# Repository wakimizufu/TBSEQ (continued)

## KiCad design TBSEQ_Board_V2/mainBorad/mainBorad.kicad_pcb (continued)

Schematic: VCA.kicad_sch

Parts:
C20, C21: 0.01uF; C_Rect_L7.2mm_W2.5mm_P5.00mm_FKS2_FKP2_MKS2_MKP2
C36: 0.033uF; C_Rect_L7.2mm_W2.5mm_P5.00mm_FKS2_FKP2_MKS2_MKP2
C37: 10uF/16V; CP_Radial_D4.0mm_P2.00mm
C41: 0.1uF; C_Rect_L7.2mm_W2.5mm_P5.00mm_FKS2_FKP2_MKS2_MKP2
C42: 1uF/50V; CP_Radial_D5.0mm_P2.00mm
D27, D35, D36: D; D_A-405_P2.54mm_Vertical_AnodeUp
IC15: CA3080A; DIP-8_W7.62mm
J4: Conn_01x02_Pin; PinHeader_1x02_P2.54mm_Horizontal
Q31: PNP; TO-92_HandSolder
Q32: NPN; TO-92_HandSolder
R119: 47K; R_Axial_DIN0207_L6.3mm_D2.5mm_P2.54mm_Vertical
R120, R134: 22K; R_Axial_DIN0207_L6.3mm_D2.5mm_P2.54mm_Vertical
R121, R131: 220K; R_Axial_DIN0207_L6.3mm_D2.5mm_P2.54mm_Vertical
R122: 100K; R_Axial_DIN0207_L6.3mm_D2.5mm_P2.54mm_Vertical
R123: 1.5M; R_Axial_DIN0207_L6.3mm_D2.5mm_P2.54mm_Vertical
R124, R125, R126, R133: 2.2K; R_Axial_DIN0207_L6.3mm_D2.5mm_P2.54mm_Vertical
R130, R132: 100; R_Axial_DIN0207_L6.3mm_D2.5mm_P2.54mm_Vertical
VCA_C_1, VCA_C_2: 10uF/16V; CP_Radial_D4.0mm_P2.00mm
VCA_IC_1: Opamp_Dual; DIP-8_W7.62mm
VCA_R1: 10K; R_Axial_DIN0207_L6.3mm_D2.5mm_P2.54mm_Vertical
VCA_R2: 100; R_Axial_DIN0207_L6.3mm_D2.5mm_P2.54mm_Vertical
VCA_R3, VCA_R5: 47K; R_Axial_DIN0207_L6.3mm_D2.5mm_P2.54mm_Vertical
VCA_R4, VCA_R6, VCA_R7: 100K; R_Axial_DIN0207_L6.3mm_D2.5mm_P2.54mm_Vertical

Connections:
A+5.333V: R126.2, VCA_IC_1.6 (-), VCA_R1.2; also elsewhere on the board
A+12V: IC15.7 (V+), R123.1, VCA_IC_1.8 (V+), VCA_R6.1; also elsewhere on the board
A+LineOut: J4.1, VCA_C_1.2, VCA_R4.1; also elsewhere on the board
A+VCA-Reso_ACC: R119.2; also elsewhere on the board
A+VCA_Control: IC15.5 (BIAS), VCA_R5.1
A+VCA_Env: D36.2 (A); also elsewhere on the board
A+VCA_Resonance: C20.1; also elsewhere on the board
A+VCA_Signal: C21.1; also elsewhere on the board
A+VCA_Trig: D35.2 (A); also elsewhere on the board
GNDA: C36.1, C37.2, C41.1, C42.2, IC15.4 (V-), J4.2, R130.2, VCA_IC_1.4 (V-), VCA_R4.2, VCA_R7.2; also elsewhere on the board
unnamed: C20.2, R122.2
unnamed: C21.2, R121.2
unnamed: C36.2, R119.1, R120.2
unnamed: C37.1, R124.2, R125.2, R126.1
unnamed: D27.2 (A), R120.1
unnamed: D27.1 (K), Q31.2 (C), VCA_R5.2
unnamed: D35.1 (K), R133.2
unnamed: D36.1 (K), R134.2
unnamed: IC15.3 (+), R121.1, R122.1, R124.1
unnamed: IC15.2 (-), R125.1
unnamed: IC15.6, VCA_C_2.1
unnamed: C42.1, Q31.3 (B), R123.2, R132.1
unnamed: Q31.1 (E), R131.1
unnamed: C41.2, Q32.3 (B), R134.1
unnamed: Q32.2 (C), R132.2
unnamed: Q32.1 (E), R130.1
unnamed: R131.2, R133.1
unnamed: VCA_C_1.1, VCA_R2.1
unnamed: VCA_IC_1.1, VCA_R2.2, VCA_R3.1
unnamed: VCA_C_2.2, VCA_IC_1.3 (+), VCA_R6.2, VCA_R7.1
unnamed: VCA_IC_1.2 (-), VCA_R1.1, VCA_R3.2
unnamed: VCA_IC_1.5 (+), VCA_IC_1.7

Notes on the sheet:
VOLUME
toJackBorad

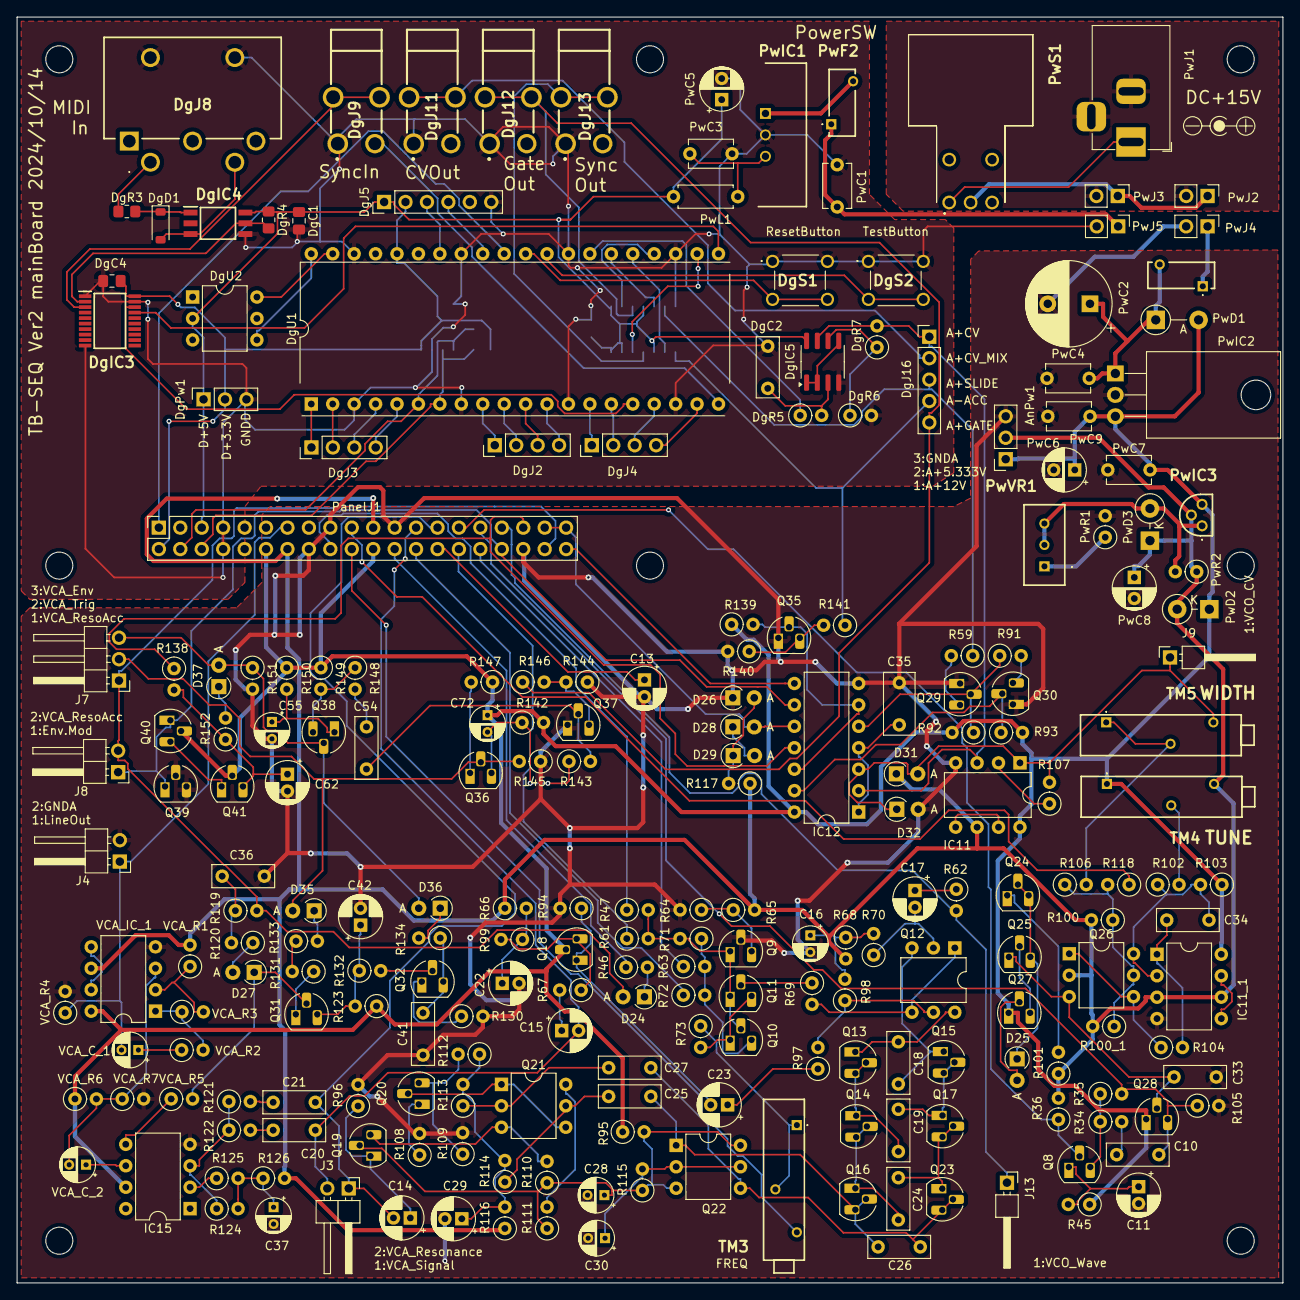
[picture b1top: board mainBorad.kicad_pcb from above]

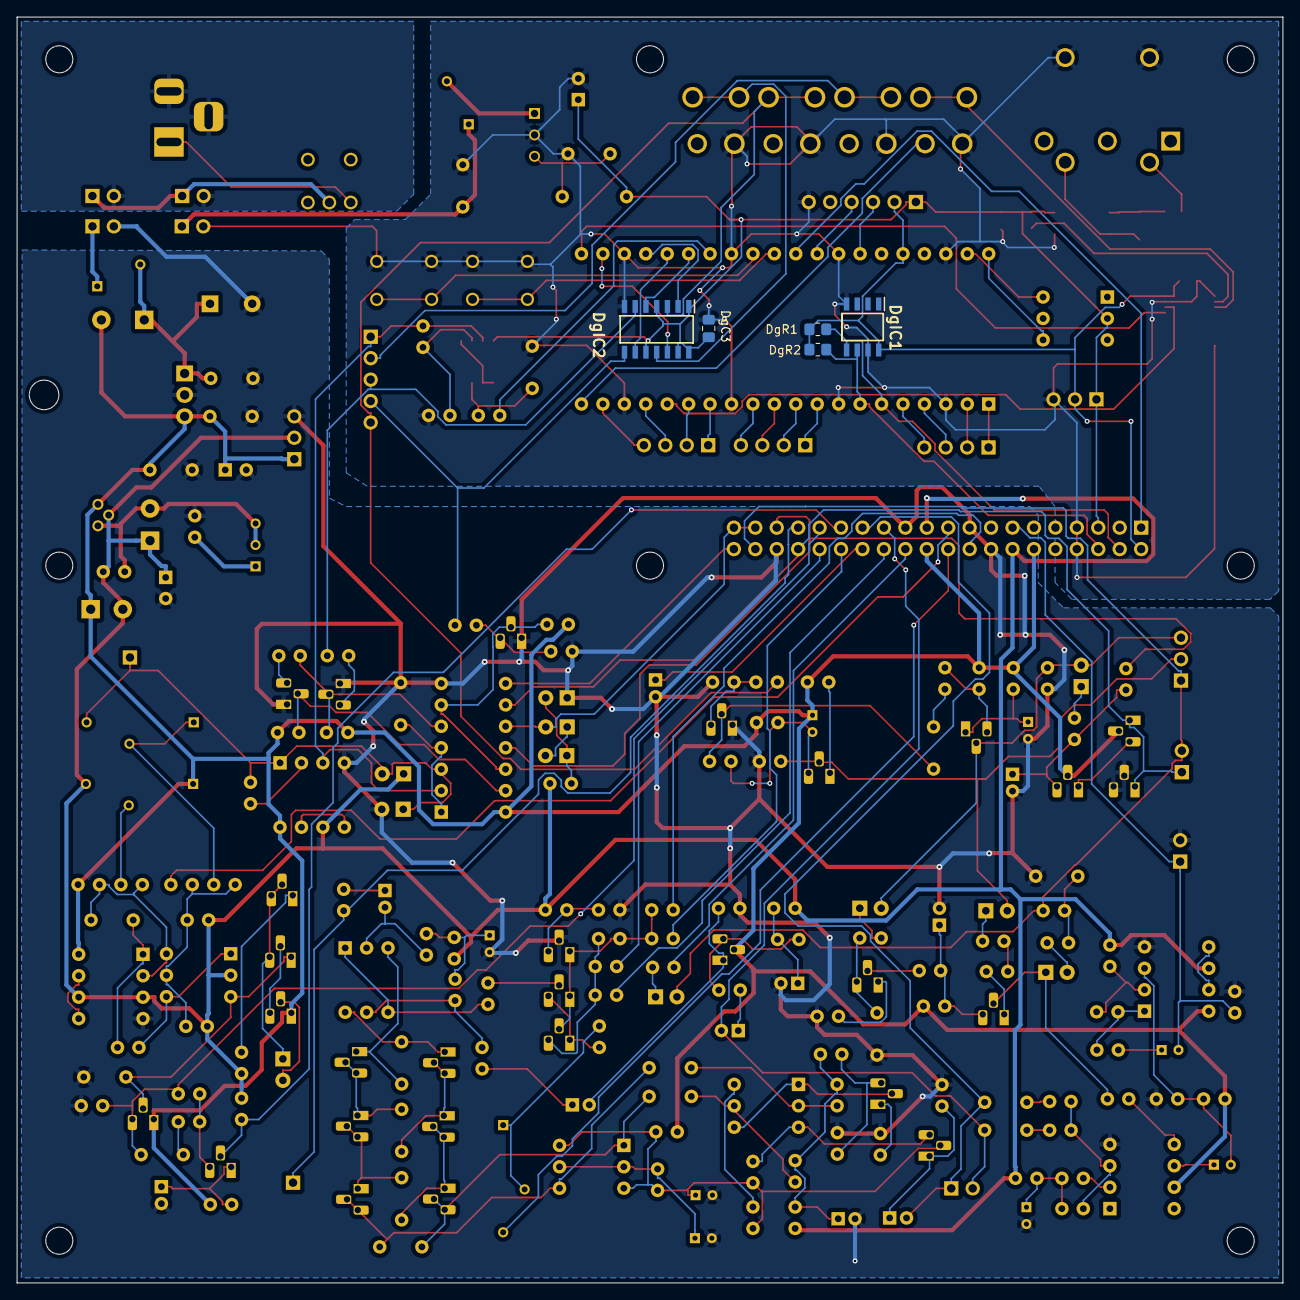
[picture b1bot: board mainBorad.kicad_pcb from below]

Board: 2 copper layers, 150.0 x 150.0 mm, 235 parts (5 on the bottom side), 176 nets.

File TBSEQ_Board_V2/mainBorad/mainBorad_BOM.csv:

"Reference","Value","Datasheet","Footprint","Qty","DNP"
"AnPw1","AnPw","~","Connector_PinSocket_2.54mm:PinSocket_1x03_P2.54mm_Vertical","1",""
"C10,C20,C21,C33","0.01uF","~","Capacitor_THT:C_Rect_L7.2mm_W2.5mm_P5.00mm_FKS2_FKP2_MKS2_MKP2","4",""
"C11,C13,C14,C15,C17,C22,C23,C29,C42,C62","1uF/50V","~","Capacitor_THT:CP_Radial_D5.0mm_P2.00mm","10",""
"C16,C30,C37,C72,VCA_C_1,VCA_C_2","10uF/16V","~","Capacitor_THT:CP_Radial_D4.0mm_P2.00mm","6",""
"C18","0.018uF","~","Capacitor_THT:C_Rect_L7.2mm_W2.5mm_P5.00mm_FKS2_FKP2_MKS2_MKP2","1",""
"C19,C24,C26,C36","0.033uF","~","Capacitor_THT:C_Rect_L7.2mm_W2.5mm_P5.00mm_FKS2_FKP2_MKS2_MKP2","4",""
"C25,C27,C41,DgC1,DgC3,DgC4,PwC4,PwC7,PwC9","0.1uF","~","-- ミックスされた値 --","9",""
"C28,C55","47uF/16V","~","Capacitor_THT:CP_Radial_D4.0mm_P2.00mm","2",""
"C34","0.001uF","~","Capacitor_THT:C_Rect_L7.2mm_W2.5mm_P5.00mm_FKS2_FKP2_MKS2_MKP2","1",""
"C35","0.22uF","~","Capacitor_THT:C_Rect_L7.2mm_W3.5mm_P5.00mm_FKS2_FKP2_MKS2_MKP2","1",""
"C54,DgC2","0.047uF","~","-- ミックスされた値 --","2",""
"D24,D25,D26,D27,D28,D29,D31,D32,D35,D36,D37","D","~","Diode_THT:D_A-405_P2.54mm_Vertical_AnodeUp","11",""
"DgD1","1N4148W","https://www.vishay.com/docs/85748/1n4148w.pdf","Diode_SMD:D_SOD-123","1",""
"DgIC1","FM24CL16B-GTR","http://www.cypress.com/file/136491/download","SamacSys_Parts:SOIC127P602X173-8N","1",""
"DgIC2","74HC126D","https://assets.nexperia.com/documents/data-sheet/74HC_HCT126.pdf","SamacSys_Parts:SOIC127P600X175-14N","1",""
"DgIC3","74LVC541APW","https://assets.nexperia.com/documents/data-sheet/74LVC541A.pdf","SOP65P640X110-20N","1",""
"DgIC4","TLP2304_TPR,E","http://toshiba.semicon-storage.com/info/docget.jsp?did=63378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","SamacSys_Parts:SOIC127P700X230-6N","1",""
"DgIC5","LM358","http://www.ti.com/lit/ds/symlink/lm2904-n.pdf","Package_SO:SOIC-8_3.9x4.9mm_P1.27mm","1",""
"DgJ2,DgJ3,DgJ4","Conn_01x04","~","Connector_PinHeader_2.54mm:PinHeader_1x04_P2.54mm_Vertical","3",""
"DgJ5","Conn_01x06","~","Connector_PinHeader_2.54mm:PinHeader_1x06_P2.54mm_Vertical","1",""
"DgJ8","KDJ03-5","https://akizukidenshi.com/download/ds/useconn/KDJ03-5.pdf","SamacSys_Parts:KDJ035","1",""
"DgJ9,DgJ11,DgJ12,DgJ13","MJ-8435","http://akizukidenshi.com/download/ds/marushin/mj8435.pdf","MJ-8435","4",""
"DgJ16","Conn_01x05","~","Connector_PinHeader_2.54mm:PinHeader_1x05_P2.54mm_Vertical","1",""
"DgPw1","DgPw","~","Connector_PinSocket_2.54mm:PinSocket_1x03_P2.54mm_Vertical","1",""
"DgR1,DgR2","1K","~","Resistor_SMD:R_0805_2012Metric_Pad1.20x1.40mm_HandSolder","2",""
"DgR3,DgR4","220","~","Resistor_SMD:R_0805_2012Metric_Pad1.20x1.40mm_HandSolder","2",""
"DgR5,R45,R110,R111,R117,R120,R134,R146,R151","22K","~","Resistor_THT:R_Axial_DIN0207_L6.3mm_D2.5mm_P2.54mm_Vertical","9",""
"DgR6,R34,R36,R47,R61,R64,R65,R94,R96,R97,R101,R105,R109,R112,R115,R116,R142,R143,R144,R145,R148,R149,VCA_R1","10K","~","Resistor_THT:R_Axial_DIN0207_L6.3mm_D2.5mm_P2.54mm_Vertical","23",""
"DgR7","5.1K","~","Resistor_THT:R_Axial_DIN0207_L6.3mm_D2.5mm_P2.54mm_Vertical","1",""
"DgS1,DgS2","B3F-1000S","https://www.mouser.com/datasheet/2/307/en-b3f-13826.pdf","SamacSys_Parts:B3F1060","2",""
"DgU1","Raspberry Pi Pico DIP-40","","SamacSys_Parts:Raspberry Pi Pico DIP-40_W17.76mm","1",""
"DgU2","IRLML6402(DIP6Convert)","","Package_DIP:DIP-6_W7.62mm","1",""
"IC11,IC11_1","AN6562","~","Package_DIP:DIP-8_W7.62mm","2",""
"IC12","4066","http://www.ti.com/lit/ds/symlink/cd4066b.pdf","Package_DIP:DIP-14_W7.62mm","1",""
"IC15","CA3080A","http://www.intersil.com/content/dam/Intersil/documents/ca30/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","Package_DIP:DIP-8_W7.62mm","1",""
"J3,J4,J8,PwJ2,PwJ3,PwJ4,PwJ5","Conn_01x02_Pin","~","-- ミックスされた値 --","7",""
"J7","Conn_01x03_Pin","~","Connector_PinHeader_2.54mm:PinHeader_1x03_P2.54mm_Horizontal","1",""
"J9,J13","Conn_01x01_Pin","~","Connector_PinHeader_2.54mm:PinHeader_1x01_P2.54mm_Horizontal","2",""
"PanelJ1","Conn_02x20_Odd_Even","~","Connector_PinSocket_2.54mm:PinSocket_2x20_P2.54mm_Vertical","1",""
"PwC1,PwC3","10uF","~","Capacitor_THT:C_Disc_D5.1mm_W3.2mm_P5.00mm","2",""
"PwC2","1000uF/25V","~","Capacitor_THT:CP_Radial_D10.0mm_P5.00mm","1",""
"PwC5","470uF/25V","~","Capacitor_THT:CP_Radial_D5.0mm_P2.50mm","1",""
"PwC6","100uF/25V","~","Capacitor_THT:CP_Radial_D5.0mm_P2.50mm","1",""
"PwC8","1uF/25V","~","Capacitor_THT:CP_Radial_D5.0mm_P2.50mm","1",""
"PwD1","SBM245L","https://www.panjit.com.tw/en/Product/downloadPDF/SBM245L","Diode_THT:D_DO-41_SOD81_P5.08mm_Vertical_AnodeUp","1",""
"PwD2,PwD3","1N4001","http://www.vishay.com/docs/88503/1n4001.pdf","Diode_THT:D_DO-41_SOD81_P3.81mm_Vertical_KathodeUp","2",""
"PwF1,PwF2","MF-R050","https://www.bourns.com/pdfs/mfr.pdf","SamacSys_Parts:MFR050","2",""
"PwIC1","BP5293-50","https://componentsearchengine.com/Datasheets/1/BP5293-50.pdf","TO254P570X1700X1780-3P","1",""
"PwIC2","L7812","http://www.st.com/content/ccc/resource/technical/document/da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","Package_TO_SOT_THT:TO-220-3_Horizontal_TabDown","1",""
"PwIC3","LM317LZG","https://www.onsemi.com/pdf/datasheet/lm317l-d.pdf","SamacSys_Parts:LM317LZG","1",""
"PwJ1","Barrel_Jack_Switch","~","Connector_BarrelJack:BarrelJack_Horizontal","1",""
"PwL1","4.7uh/0.5A","~","Resistor_THT:R_Axial_DIN0207_L6.3mm_D2.5mm_P7.62mm_Horizontal","1",""
"PwR1","330","~","Resistor_THT:R_Axial_DIN0207_L6.3mm_D2.5mm_P2.54mm_Vertical","1",""
"PwR2","120","~","Resistor_THT:R_Axial_DIN0207_L6.3mm_D2.5mm_P2.54mm_Vertical","1",""
"PwS1","4MS1R202M6QES","","SamacSys_Parts:4MS1R202M6QES","1",""
"PwVR1","3296W-1-101LF","https://www.bourns.com/docs/product-datasheets/3296.pdf","SamacSys_Parts:3296W1502A","1",""
"Q8,Q9,Q10,Q27,Q31,Q36,Q38","PNP","~","Package_TO_SOT_THT:TO-92_HandSolder","7",""
"Q11,Q13,Q14,Q15,Q16,Q17,Q18,Q19,Q20,Q23,Q24,Q25,Q29,Q30,Q32,Q35,Q37,Q40,Q41","NPN","~","Package_TO_SOT_THT:TO-92_HandSolder","19",""
"Q12,Q21,Q22,Q26","HN1C01FU-GR,LF_6P DIP","https://toshiba.semicon-storage.com/info/HN4A06J_datasheet_e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","Package_DIP:DIP-6_W7.62mm","4",""
"Q28,Q39","NJFET","~","Package_TO_SOT_THT:TO-92_HandSolder","2",""
"R35,R59,R66,R72,R73,R92,R93,R99,R102,R113,R114,R118,R122,R139,R140,R141,VCA_R4,VCA_R6,VCA_R7","100K","~","Resistor_THT:R_Axial_DIN0207_L6.3mm_D2.5mm_P2.54mm_Vertical","19",""
"R46,R119,VCA_R3,VCA_R5","47K","~","Resistor_THT:R_Axial_DIN0207_L6.3mm_D2.5mm_P2.54mm_Vertical","4",""
"R62,R63,R103,R121,R131","220K","~","Resistor_THT:R_Axial_DIN0207_L6.3mm_D2.5mm_P2.54mm_Vertical","5",""
"R67,R68,R69,R70,R71,R98,R104,R107,R108,R124,R125,R126,R133","2.2K","~","Resistor_THT:R_Axial_DIN0207_L6.3mm_D2.5mm_P2.54mm_Vertical","13",""
"R91","1M","~","Resistor_THT:R_Axial_DIN0207_L6.3mm_D2.5mm_P2.54mm_Vertical","1",""
"R95,R130,R132,R152,VCA_R2","100","~","Resistor_THT:R_Axial_DIN0207_L6.3mm_D2.5mm_P2.54mm_Vertical","5",""
"R100,R100_1","1K(TEMPCO)","~","Resistor_THT:R_Axial_DIN0207_L6.3mm_D2.5mm_P2.54mm_Vertical","2",""
"R106","27K","~","Resistor_THT:R_Axial_DIN0207_L6.3mm_D2.5mm_P2.54mm_Vertical","1",""
"R123","1.5M","~","Resistor_THT:R_Axial_DIN0207_L6.3mm_D2.5mm_P2.54mm_Vertical","1",""
"R138","68K","~","Resistor_THT:R_Axial_DIN0207_L6.3mm_D2.5mm_P2.54mm_Vertical","1",""
"R147,R150","22","~","Resistor_THT:R_Axial_DIN0207_L6.3mm_D2.5mm_P2.54mm_Vertical","2",""
"TM3","500K","https://www.bourns.com/docs/Product-Datasheets/3006.pdf","3006P1503LF","1",""
"TM4","50K","https://www.bourns.com/docs/Product-Datasheets/3006.pdf","SamacSys_Parts:3006P1503LF","1",""
"TM5","5K","https://www.bourns.com/docs/Product-Datasheets/3006.pdf","3006P1503LF","1",""
"VCA_IC_1","Opamp_Dual","~","-- ミックスされた値 --","1",""
